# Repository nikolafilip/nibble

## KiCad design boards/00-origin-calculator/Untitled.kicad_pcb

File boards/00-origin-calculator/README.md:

# The origin: a hand-made 3-bit calculator

This is the KiCad project the whole thing started from, exactly as it was on
2026-08-17. Nothing in this directory is edited, ever.

Built by hand, from scratch, while relearning electronics: a keypad encoder, a
3-bit sign-magnitude adder/subtractor built from 2N3904 RTL gates, a result
register, a 4-to-16 decoder for a display, and a reference NOR/NAND pair.
419 transistors, 1,087 resistors. Simulated in KiCad's ngspice integration.

It has bugs. They are listed in `docs/KNOWN-ISSUES.md` and are fixed by the
redesign in `boards/01-alu`, not here.

The SPICE model path inside the schematic points at the Desktop location the
original used; the model is in `lib/2N3904.lib`. The PCB has 747 of about 1,500
footprints placed and no tracks: routing is where the original run stopped.

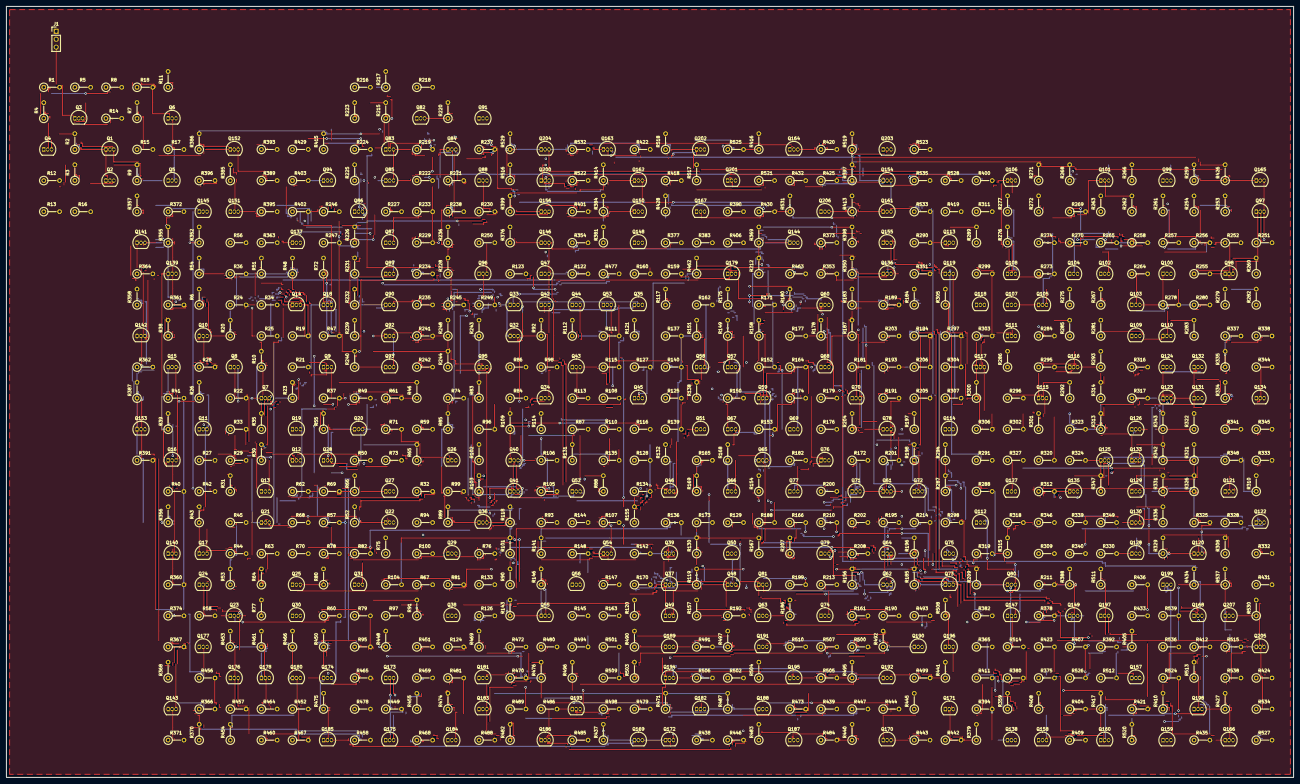
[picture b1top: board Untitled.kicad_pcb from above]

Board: 2 copper layers, 414.0 x 248.0 mm, 747 parts (0 on the bottom side), 386 nets.

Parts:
J1: PWR; PinHeader_1x03_P2.54mm_Vertical
Q1, Q2, Q3, Q4, Q5, Q6, Q7, Q8, Q9, Q10, Q11, Q12, Q13, Q14, Q15, Q16, Q17, Q18, Q19, Q20, Q21, Q22, Q23, Q24, Q25, Q26, Q27, Q28, Q29, Q30, Q31, Q32, Q33, Q34, Q35, Q36, Q37, Q38, Q39, Q40, Q41, Q42, Q43, Q44, Q45, Q46, Q47, Q48, Q49, Q50, Q51, Q52, Q53, Q54, Q55, Q56, Q57, Q58, Q59, Q60, Q61, Q62, Q63, Q64, Q65, Q66, Q67, Q68, Q69, Q70, Q71, Q72, Q73, Q74, Q75, Q76, Q77, Q78, Q79, Q80, Q81, Q82, Q83, Q84, Q85, Q86, Q87, Q88, Q89, Q90, Q91, Q92, Q93, Q94, Q95, Q96, Q97, Q98, Q99, Q100, Q101, Q102, Q103, Q104, Q105, Q106, Q107, Q108, Q109, Q110, Q111, Q112, Q113, Q114, Q115, Q116, Q117, Q118, Q119, Q120, Q121, Q122, Q123, Q124, Q125, Q126, Q127, Q128, Q129, Q130, Q131, Q132, Q133, Q134, Q135, Q136, Q137, Q138, Q139, Q140, Q141, Q142, Q143, Q144, Q145, Q146, Q147, Q148, Q149, Q150, Q151, Q152, Q153, Q154, Q155, Q156, Q157, Q158, Q159, Q160, Q161, Q162, Q163, Q164, Q165, Q166, Q167, Q168, Q169, Q170, Q171, Q172, Q173, Q174, Q175, Q176, Q177, Q178, Q179, Q180, Q181, Q182, Q183, Q184, Q185, Q186, Q187, Q188, Q189, Q190, Q191, Q192, Q193, Q194, Q195, Q196, Q197, Q198, Q199, Q200, Q201, Q202, Q203, Q204, Q205, Q206, Q207: 2N3904; TO-92_Inline
R1, R5, R8, R18, R21, R25, R29, R34, R37, R42, R45, R49, R61, R62, R63, R70, R71, R74, R78, R82, R86, R98, R99, R100, R107, R108, R111, R115, R127, R128, R129, R136, R137, R140, R144, R148, R152, R164, R165, R166, R173, R174, R177, R181, R193, R194, R195, R202, R203, R206, R210, R214, R218, R222, R233, R238, R245, R250, R259, R266, R275, R282, R283, R286, R290, R298, R299, R304, R307, R311, R319, R320, R325, R328, R332, R340, R341, R346, R349, R353, R365, R366, R367, R374, R375, R378, R382, R394, R395, R396, R403, R404, R407, R411, R423, R424, R425, R432, R433, R436, R439, R444, R447, R451, R459, R460, R465, R468, R472, R480, R481, R486, R489, R493, R501, R502, R507, R510, R514, R526, R527, R528, R535, R536, R539: 4.7k; R_Axial_DIN0207_L6.3mm_D2.5mm_P5.08mm_Vertical
R2, R3, R4, R6, R7, R9, R10, R11, R20, R23, R26, R30, R31, R35, R38, R39, R43, R46, R48, R51, R52, R53, R54, R55, R64, R65, R66, R72, R75, R77, R80, R83, R85, R88, R89, R90, R91, R92, R101, R102, R103, R109, R112, R114, R117, R118, R119, R120, R121, R130, R131, R132, R138, R141, R143, R146, R149, R151, R154, R155, R156, R157, R158, R167, R168, R169, R175, R178, R180, R183, R184, R185, R186, R187, R196, R197, R198, R204, R207, R209, R212, R215, R217, R220, R223, R225, R226, R228, R231, R232, R236, R239, R240, R243, R244, R248, R251, R252, R255, R256, R257, R258, R264, R265, R269, R270, R273, R274, R278, R280, R284, R287, R289, R292, R293, R294, R300, R301, R305, R308, R310, R313, R314, R315, R321, R322, R326, R329, R331, R334, R335, R336, R342, R343, R347, R350, R352, R355, R356, R357, R358, R359, R368, R369, R370, R376, R379, R381, R384, R385, R386, R387, R388, R397, R398, R399, R405, R408, R410, R413, R414, R415, R416, R417, R426, R427, R428, R434, R437, R440, R441, R445, R448, R450, R453, R454, R455, R461, R462, R466, R469, R471, R474, R475, R476, R482, R483, R487, R490, R492, R495, R496, R497, R503, R504, R508, R511, R513, R516, R517, R518, R519, R520, R529, R530, R531, R537: 10k; R_Axial_DIN0207_L6.3mm_D2.5mm_P5.08mm_Vertical
R12, R13, R14, R15, R16, R17, R19, R22, R24, R27, R28, R32, R33, R36, R40, R41, R44, R47, R50, R56, R57, R58, R59, R60, R67, R68, R69, R73, R76, R79, R81, R84, R87, R93, R94, R95, R96, R97, R104, R105, R106, R110, R113, R116, R122, R123, R124, R125, R126, R133, R134, R135, R139, R142, R145, R147, R150, R153, R159, R160, R161, R162, R163, R170, R171, R172, R176, R179, R182, R188, R189, R190, R191, R192, R199, R200, R201, R205, R208, R211, R213, R216, R219, R221, R224, R227, R229, R230, R234, R235, R237, R241, R242, R246, R247, R249, R253, R254, R260, R261, R262, R263, R267, R268, R271, R272, R276, R277, R279, R281, R285, R288, R291, R295, R296, R297, R302, R303, R306, R309, R312, R316, R317, R318, R323, R324, R327, R330, R333, R337, R338, R339, R344, R345, R348, R351, R354, R360, R361, R362, R363, R364, R371, R372, R373, R377, R380, R383, R389, R390, R391, R392, R393, R400, R401, R402, R406, R409, R412, R418, R419, R420, R421, R422, R429, R430, R431, R435, R438, R442, R443, R446, R449, R452, R456, R457, R458, R463, R464, R467, R470, R473, R477, R478, R479, R484, R485, R488, R491, R494, R498, R499, R500, R505, R506, R509, R512, R515, R521, R522, R523, R524, R525, R532, R533, R534, R538: 22k; R_Axial_DIN0207_L6.3mm_D2.5mm_P5.08mm_Vertical

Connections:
+5V: J1.2, R1.1, R2.1, R3.1, R5.1, R7.1, R8.1, R9.1, R18.1, R21.1, R25.1, R29.1, R34.1, R37.1, R42.1, R45.1, R49.1, R61.1, R62.1, R63.1, R70.1, R71.1, R74.1, R78.1, R82.1, R86.1, R98.1, R99.1, R100.1, R107.1, R108.1, R111.1, R115.1, R127.1, R128.1, R129.1, R136.1, R137.1, R140.1, R144.1, R148.1, R152.1, R164.1, R165.1, R166.1, R173.1, R174.1, R177.1, R181.1, R193.1, R194.1, R195.1, R202.1, R203.1, R206.1, R210.1, R214.1, R218.1, R222.1, R232.1, R233.1, R238.1, R245.1, R250.1, R255.1, R259.1, R264.1, R266.1, R275.1, R282.1, R283.1, R286.1, R290.1, R298.1, R299.1, R304.1, R307.1, R311.1, R319.1, R320.1, R325.1, R328.1, R332.1, R340.1, R341.1, R346.1, R349.1, R353.1, R365.1, R366.1, R367.1, R374.1, R375.1, R378.1, R382.1, R394.1, R395.1, R396.1, R403.1, R404.1, R407.1, R411.1, R423.1, R424.1, R425.1, R432.1, R433.1, R436.1, R439.1, R444.1, R447.1, R451.1, R459.1, R460.1, R465.1, R468.1, R472.1, R480.1, R481.1, R486.1, R489.1, R493.1, R501.1, R502.1, R507.1, R510.1, R514.1, R526.1, R527.1, R528.1, R535.1, R536.1, R539.1
/A0: Q96.3 (C), R6.1, R10.1, R38.1, R250.2
/A1: Q91.3 (C), R83.1, R88.1, R90.1, R238.2
/A2: Q84.3 (C), R149.1, R154.1, R156.1, R222.2
/B0: Q119.3 (C), R20.1, R26.1, R39.1, R307.2
/B1: Q127.3 (C), R85.1, R89.1, R91.1, R328.2
/B2: Q135.3 (C), R151.1, R155.1, R157.1, R349.2
/Cin1: Q31.3 (C), R82.2, R114.1, R118.1, R120.1
/Cin2: Q56.3 (C), R148.2, R180.1, R184.1, R186.1
/EB0: Q111.3 (C), R286.2, R289.1, R293.1
/EB1: Q110.3 (C), R283.2, R310.1, R314.1
/EB2: Q109.3 (C), R282.2, R331.1, R335.1
/OUT0: Q146.3 (C), R378.2
/OUT1: Q157.3 (C), R407.2
/OUT2: Q168.3 (C), R436.2
/OUT3: Q207.3 (C), R539.2
/OUT4: Q204.3 (C), R535.2
/S0: Q28.3 (C), R74.2, R448.1, R453.1
/S1: Q53.3 (C), R140.2, R469.1, R474.1
/S2: Q78.3 (C), R206.2, R490.1, R495.1
/S3: Q81.3 (C), R214.2, R437.1, R511.1, R516.1, R518.1
/X3: R258.1, R270.1
/X5: R252.1, R273.1
/X7: R251.1, R257.1, R269.1
/Y3: R228.1, R240.1
/Y5: R223.1, R243.1
/Y6: R217.1, R231.1
/Y7: R215.1, R226.1, R239.1
GND: J1.1, Q2.1 (E), Q3.1 (E), Q4.1 (E), Q5.1 (E), Q6.1 (E), Q7.1 (E), Q8.1 (E), Q9.1 (E), Q11.1 (E), Q13.1 (E), Q14.1 (E), Q16.1 (E), Q17.1 (E), Q18.1 (E), Q19.1 (E), Q20.1 (E), Q22.1 (E), Q24.1 (E), Q25.1 (E), Q27.1 (E), Q28.1 (E), Q29.1 (E), Q30.1 (E), Q31.1 (E), Q32.1 (E), Q33.1 (E), Q34.1 (E), Q36.1 (E), Q38.1 (E), Q39.1 (E), Q41.1 (E), Q42.1 (E), Q43.1 (E), Q44.1 (E), Q45.1 (E), Q47.1 (E), Q49.1 (E), Q50.1 (E), Q52.1 (E), Q53.1 (E), Q54.1 (E), Q55.1 (E), Q56.1 (E), Q57.1 (E), Q58.1 (E), Q59.1 (E), Q61.1 (E), Q63.1 (E), Q64.1 (E), Q66.1 (E), Q67.1 (E), Q68.1 (E), Q69.1 (E), Q70.1 (E), Q72.1 (E), Q74.1 (E), Q75.1 (E), Q77.1 (E), Q78.1 (E), Q79.1 (E), Q80.1 (E), Q81.1 (E), Q82.1 (E), Q83.1 (E), Q84.1 (E), Q85.1 (E), Q86.1 (E), Q87.1 (E), Q88.1 (E), Q89.1 (E), Q90.1 (E), Q91.1 (E), Q92.1 (E), Q93.1 (E), Q94.1 (E), Q95.1 (E), Q96.1 (E), Q97.1 (E), Q98.1 (E), Q99.1 (E), Q100.1 (E), Q101.1 (E), Q102.1 (E), Q103.1 (E), Q104.1 (E), Q105.1 (E), Q106.1 (E), Q107.1 (E), Q108.1 (E), Q109.1 (E), Q110.1 (E), Q111.1 (E), Q112.1 (E), Q113.1 (E), Q114.1 (E), Q116.1 (E), Q118.1 (E), Q119.1 (E), Q120.1 (E), Q121.1 (E), Q122.1 (E), Q124.1 (E), Q126.1 (E), Q127.1 (E), Q128.1 (E), Q129.1 (E), Q130.1 (E), Q132.1 (E), Q134.1 (E), Q135.1 (E), Q136.1 (E), Q137.1 (E), Q138.1 (E), Q140.1 (E), Q142.1 (E), Q143.1 (E), Q145.1 (E), Q146.1 (E), Q147.1 (E), Q148.1 (E), Q149.1 (E), Q151.1 (E), Q153.1 (E), Q154.1 (E), Q156.1 (E), Q157.1 (E), Q158.1 (E), Q159.1 (E), Q160.1 (E), Q162.1 (E), Q164.1 (E), Q165.1 (E), Q167.1 (E), Q168.1 (E), Q169.1 (E), Q171.1 (E), Q172.1 (E), Q173.1 (E), Q174.1 (E), Q175.1 (E), Q177.1 (E), Q179.1 (E), Q180.1 (E), Q181.1 (E), Q182.1 (E), Q183.1 (E), Q185.1 (E), Q187.1 (E), Q188.1 (E), Q189.1 (E), Q190.1 (E), Q191.1 (E), Q193.1 (E), Q195.1 (E), Q196.1 (E), Q197.1 (E), Q198.1 (E), Q199.1 (E), Q201.1 (E), Q203.1 (E), Q204.1 (E), Q206.1 (E), Q207.1 (E), R12.1, R13.1, R14.1, R15.1, R16.1, R17.1, R19.1, R22.1, R24.1, R27.1, R28.1, R32.1, R33.1, R36.1, R40.1, R41.1, R44.1, R47.1, R50.1, R56.1, R57.1, R58.1, R59.1, R60.1, R67.1, R68.1, R69.1, R73.1, R76.1, R79.1, R81.1, R84.1, R87.1, R93.1, R94.1, R95.1, R96.1, R97.1, R104.1, R105.1, R106.1, R110.1, R113.1, R116.1, R122.1, R123.1, R124.1, R125.1, R126.1, R133.1, R134.1, R135.1, R139.1, R142.1, R145.1, R147.1, R150.1, R153.1, R159.1, R160.1, R161.1, R162.1, R163.1, R170.1, R171.1, R172.1, R176.1, R179.1, R182.1, R188.1, R189.1, R190.1, R191.1, R192.1, R199.1, R200.1, R201.1, R205.1, R208.1, R211.1, R213.1, R216.1, R219.1, R221.1, R224.1, R227.1, R229.1, R230.1, R234.1, R235.1, R237.1, R241.1, R242.1, R246.1, R247.1, R249.1, R253.1, R254.1, R260.1, R261.1, R262.1, R263.1, R267.1, R268.1, R271.1, R272.1, R276.1, R277.1, R279.1, R281.1, R285.1, R288.1, R291.1, R295.1, R296.1, R297.1, R302.1, R303.1, R306.1, R309.1, R312.1, R316.1, R317.1, R318.1, R323.1, R324.1, R327.1, R330.1, R333.1, R337.1, R338.1, R339.1, R344.1, R345.1, R348.1, R351.1, R354.1, R360.1, R361.1, R362.1, R363.1, R364.1, R371.1, R372.1, R373.1, R377.1, R380.1, R383.1, R389.1, R390.1, R391.1, R392.1, R393.1, R400.1, R401.1, R402.1, R406.1, R409.1, R412.1, R418.1, R419.1, R420.1, R421.1, R422.1, R429.1, R430.1, R431.1, R435.1, R438.1, R442.1, R443.1, R446.1, R449.1, R452.1, R456.1, R457.1, R458.1, R463.1, R464.1, R467.1, R470.1, R473.1, R477.1, R478.1, R479.1, R484.1, R485.1, R488.1, R491.1, R494.1, R498.1, R499.1, R500.1, R505.1, R506.1, R509.1, R512.1, R515.1, R521.1, R522.1, R523.1, R524.1, R525.1, R532.1, R533.1, R534.1, R538.1
unnamed: Q1.2 (B), R2.2, R12.2
unnamed: Q1.3 (C), R1.2, R4.1
unnamed: Q1.1 (E), Q2.3 (C)
unnamed: Q2.2 (B), R3.2, R13.2
unnamed: Q3.2 (B), R4.2, R14.2
unnamed: Q3.3 (C), R5.2
unnamed: Q4.2 (B), R7.2, R15.2
unnamed: Q4.3 (C), Q5.3 (C), R8.2, R11.1
unnamed: Q5.2 (B), R9.2, R16.2
unnamed: Q6.2 (B), R11.2, R17.2
unnamed: Q6.3 (C), R18.2
unnamed: Q7.2 (B), R10.2, R19.2
unnamed: Q7.3 (C), Q8.3 (C), R21.2, R23.1
unnamed: Q8.2 (B), R20.2, R22.2
unnamed: Q9.2 (B), R23.2, R24.2
unnamed: Q9.3 (C), R25.2, R30.1
unnamed: Q10.2 (B), R6.2, R28.2
unnamed: Q10.3 (C), R29.2, R31.1
unnamed: Q10.1 (E), Q11.3 (C)
unnamed: Q11.2 (B), R26.2, R27.2
unnamed: Q12.2 (B), R30.2, R33.2
unnamed: Q12.3 (C), R34.2, R35.1
unnamed: Q12.1 (E), Q13.3 (C)
unnamed: Q13.2 (B), R31.2, R32.2
unnamed: Q14.2 (B), R35.2, R36.2
unnamed: Q14.3 (C), R37.2, R46.1, R51.1, R53.1
unnamed: Q15.2 (B), R38.2, R41.2
unnamed: Q15.3 (C), R42.2, R43.1
unnamed: Q15.1 (E), Q16.3 (C)
unnamed: Q16.2 (B), R39.2, R40.2
unnamed: Q17.2 (B), R43.2, R44.2
unnamed: Q17.3 (C), R45.2, R77.1
unnamed: Q18.2 (B), R46.2, R47.2
unnamed: Q18.3 (C), Q19.3 (C), R49.2, R55.1
unnamed: Q19.2 (B), R48.2, R50.2
unnamed: Q20.2 (B), R55.2, R59.2
unnamed: Q20.3 (C), R61.2, R65.1
unnamed: Q21.2 (B), R51.2, R57.2
unnamed: Q21.3 (C), R62.2, R66.1
unnamed: Q21.1 (E), Q22.3 (C)
unnamed: Q22.2 (B), R52.2, R56.2
unnamed: Q23.2 (B), R53.2, R60.2
unnamed: Q23.3 (C), R63.2, R64.1
unnamed: Q23.1 (E), Q24.3 (C)
unnamed: Q24.2 (B), R54.2, R58.2
unnamed: Q25.2 (B), R64.2, R67.2
unnamed: Q25.3 (C), R70.2, R75.1
unnamed: Q26.2 (B), R65.2, R69.2
unnamed: Q26.3 (C), R71.2, R72.1
unnamed: Q26.1 (E), Q27.3 (C)
unnamed: Q27.2 (B), R66.2, R68.2
unnamed: Q28.2 (B), R72.2, R73.2
unnamed: Q29.2 (B), R75.2, R76.2
unnamed: Q29.3 (C), Q30.3 (C), R78.2, R80.1
unnamed: Q30.2 (B), R77.2, R79.2
unnamed: Q31.2 (B), R80.2, R81.2
unnamed: Q32.2 (B), R83.2, R84.2
unnamed: Q32.3 (C), Q33.3 (C), R86.2, R92.1
unnamed: Q33.2 (B), R85.2, R87.2
unnamed: Q34.2 (B), R92.2, R96.2
unnamed: Q34.3 (C), R98.2, R102.1
unnamed: Q35.2 (B), R88.2, R94.2
unnamed: Q35.3 (C), R99.2, R103.1
unnamed: Q35.1 (E), Q36.3 (C)
unnamed: Q36.2 (B), R89.2, R93.2
unnamed: Q37.2 (B), R90.2, R97.2
unnamed: Q37.3 (C), R100.2, R101.1
unnamed: Q37.1 (E), Q38.3 (C)
unnamed: Q38.2 (B), R91.2, R95.2
unnamed: Q39.2 (B), R101.2, R104.2
unnamed: Q39.3 (C), R107.2, R143.1
unnamed: Q40.2 (B), R102.2, R106.2
unnamed: Q40.3 (C), R108.2, R109.1
unnamed: Q40.1 (E), Q41.3 (C)
unnamed: Q41.2 (B), R103.2, R105.2
unnamed: Q42.2 (B), R109.2, R110.2
unnamed: Q42.3 (C), R111.2, R112.1, R117.1, R119.1
unnamed: Q43.2 (B), R112.2, R113.2
unnamed: Q43.3 (C), Q44.3 (C), R115.2, R121.1
unnamed: Q44.2 (B), R114.2, R116.2
unnamed: Q45.2 (B), R121.2, R125.2
unnamed: Q45.3 (C), R127.2, R131.1
unnamed: Q46.2 (B), R117.2, R123.2
unnamed: Q46.3 (C), R128.2, R132.1
unnamed: Q46.1 (E), Q47.3 (C)
unnamed: Q47.2 (B), R118.2, R122.2
unnamed: Q48.2 (B), R119.2, R126.2
unnamed: Q48.3 (C), R129.2, R130.1
unnamed: Q48.1 (E), Q49.3 (C)
unnamed: Q49.2 (B), R120.2, R124.2
unnamed: Q50.2 (B), R130.2, R133.2
unnamed: Q50.3 (C), R136.2, R141.1
unnamed: Q51.2 (B), R131.2, R135.2
unnamed: Q51.3 (C), R137.2, R138.1
unnamed: Q51.1 (E), Q52.3 (C)
unnamed: Q52.2 (B), R132.2, R134.2
unnamed: Q53.2 (B), R138.2, R139.2
unnamed: Q54.2 (B), R141.2, R142.2
unnamed: Q54.3 (C), Q55.3 (C), R144.2, R146.1
unnamed: Q55.2 (B), R143.2, R145.2
unnamed: Q56.2 (B), R146.2, R147.2
unnamed: Q57.2 (B), R149.2, R150.2
unnamed: Q57.3 (C), Q58.3 (C), R152.2, R158.1
unnamed: Q58.2 (B), R151.2, R153.2
unnamed: Q59.2 (B), R158.2, R162.2
unnamed: Q59.3 (C), R164.2, R168.1
unnamed: Q60.2 (B), R154.2, R160.2
unnamed: Q60.3 (C), R165.2, R169.1
unnamed: Q60.1 (E), Q61.3 (C)
unnamed: Q61.2 (B), R155.2, R159.2
unnamed: Q62.2 (B), R156.2, R163.2
unnamed: Q62.3 (C), R166.2, R167.1
unnamed: Q62.1 (E), Q63.3 (C)
unnamed: Q63.2 (B), R157.2, R161.2
unnamed: Q64.2 (B), R167.2, R170.2
unnamed: Q64.3 (C), R173.2, R209.1
unnamed: Q65.2 (B), R168.2, R172.2
unnamed: Q65.3 (C), R174.2, R175.1
unnamed: Q65.1 (E), Q66.3 (C)
unnamed: Q66.2 (B), R169.2, R171.2
unnamed: Q67.2 (B), R175.2, R176.2
unnamed: Q67.3 (C), R177.2, R178.1, R183.1, R185.1
unnamed: Q68.2 (B), R178.2, R179.2
unnamed: Q68.3 (C), Q69.3 (C), R181.2, R187.1
unnamed: Q69.2 (B), R180.2, R182.2
unnamed: Q70.2 (B), R187.2, R191.2
unnamed: Q70.3 (C), R193.2, R197.1
unnamed: Q71.2 (B), R183.2, R189.2
unnamed: Q71.3 (C), R194.2, R198.1
unnamed: Q71.1 (E), Q72.3 (C)
unnamed: Q72.2 (B), R184.2, R188.2
unnamed: Q73.2 (B), R185.2, R192.2
unnamed: Q73.3 (C), R195.2, R196.1
unnamed: Q73.1 (E), Q74.3 (C)
unnamed: Q74.2 (B), R186.2, R190.2
unnamed: Q75.2 (B), R196.2, R199.2
unnamed: Q75.3 (C), R202.2, R207.1
unnamed: Q76.2 (B), R197.2, R201.2
unnamed: Q76.3 (C), R203.2, R204.1
unnamed: Q76.1 (E), Q77.3 (C)
unnamed: Q77.2 (B), R198.2, R200.2
unnamed: Q78.2 (B), R204.2, R205.2
unnamed: Q79.2 (B), R207.2, R208.2
unnamed: Q79.3 (C), Q80.3 (C), R210.2, R212.1
unnamed: Q80.2 (B), R209.2, R211.2
unnamed: Q81.2 (B), R212.2, R213.2
unnamed: Q82.2 (B), R215.2, R216.2
unnamed: Q82.3 (C), Q83.3 (C), Q85.3 (C), Q86.3 (C), R218.2, R220.1
unnamed: Q83.2 (B), R217.2, R219.2
unnamed: Q84.2 (B), R220.2, R221.2
unnamed: Q85.2 (B), R223.2, R224.2
unnamed: Q86.2 (B), R225.2, R227.2
unnamed: Q87.2 (B), R226.2, R229.2
unnamed: Q87.3 (C), Q88.3 (C), Q89.3 (C), Q90.3 (C), R233.2, R236.1
unnamed: Q88.2 (B), R228.2, R230.2
unnamed: Q89.2 (B), R231.2, R234.2
unnamed: Q90.2 (B), R232.2, R235.2
unnamed: Q91.2 (B), R236.2, R237.2
unnamed: Q92.2 (B), R239.2, R241.2
unnamed: Q92.3 (C), Q93.3 (C), Q94.3 (C), Q95.3 (C), R245.2, R248.1
unnamed: Q93.2 (B), R240.2, R242.2
unnamed: Q94.2 (B), R243.2, R246.2
unnamed: Q95.2 (B), R244.2, R247.2
unnamed: Q96.2 (B), R248.2, R249.2
unnamed: Q97.2 (B), R251.2, R253.2
unnamed: Q98.2 (B), R252.2, R254.2
unnamed: Q99.2 (B), R255.2, R260.2
unnamed: Q100.2 (B), R256.2, R261.2
unnamed: Q97.3 (C), Q98.3 (C), Q99.3 (C), Q100.3 (C), R259.2, R278.1
unnamed: Q101.2 (B), R257.2, R262.2
unnamed: Q101.3 (C), Q102.3 (C), Q103.3 (C), Q104.3 (C), R266.2, R280.1
unnamed: Q102.2 (B), R258.2, R263.2
unnamed: Q103.2 (B), R264.2, R267.2
unnamed: Q104.2 (B), R265.2, R268.2
unnamed: Q105.2 (B), R269.2, R271.2
unnamed: Q105.3 (C), Q106.3 (C), Q107.3 (C), Q108.3 (C), R275.2, R284.1
unnamed: Q106.2 (B), R270.2, R272.2
unnamed: Q107.2 (B), R273.2, R276.2
unnamed: Q108.2 (B), R274.2, R277.2
unnamed: Q109.2 (B), R278.2, R279.2
unnamed: Q110.2 (B), R280.2, R281.2
unnamed: Q111.2 (B), R284.2, R285.2
unnamed: Q112.2 (B), R287.2, R288.2
unnamed: Q112.3 (C), Q113.3 (C), R290.2, R294.1
unnamed: Q113.2 (B), R289.2, R291.2
unnamed: Q114.2 (B), R294.2, R297.2
unnamed: Q114.3 (C), R298.2, R300.1
unnamed: Q115.2 (B), R292.2, R296.2
unnamed: Q115.3 (C), R299.2, R301.1
unnamed: Q115.1 (E), Q116.3 (C)
unnamed: Q116.2 (B), R293.2, R295.2
unnamed: Q117.2 (B), R300.2, R303.2
unnamed: Q117.3 (C), R304.2, R305.1
unnamed: Q117.1 (E), Q118.3 (C)
unnamed: Q118.2 (B), R301.2, R302.2
unnamed: Q119.2 (B), R305.2, R306.2
unnamed: Q120.2 (B), R308.2, R309.2
unnamed: Q120.3 (C), Q121.3 (C), R311.2, R315.1
unnamed: Q121.2 (B), R310.2, R312.2
unnamed: Q122.2 (B), R315.2, R318.2
unnamed: Q122.3 (C), R319.2, R321.1
unnamed: Q123.2 (B), R313.2, R317.2
unnamed: Q123.3 (C), R320.2, R322.1
unnamed: Q123.1 (E), Q124.3 (C)
unnamed: Q124.2 (B), R314.2, R316.2
unnamed: Q125.2 (B), R321.2, R324.2
unnamed: Q125.3 (C), R325.2, R326.1
unnamed: Q125.1 (E), Q126.3 (C)
unnamed: Q126.2 (B), R322.2, R323.2
unnamed: Q127.2 (B), R326.2, R327.2
unnamed: Q128.2 (B), R329.2, R330.2
unnamed: Q128.3 (C), Q129.3 (C), R332.2, R336.1
unnamed: Q129.2 (B), R331.2, R333.2
unnamed: Q130.2 (B), R336.2, R339.2
unnamed: Q130.3 (C), R340.2, R342.1
unnamed: Q131.2 (B), R334.2, R338.2
unnamed: Q131.3 (C), R341.2, R343.1
unnamed: Q131.1 (E), Q132.3 (C)
unnamed: Q132.2 (B), R335.2, R337.2
unnamed: Q133.2 (B), R342.2, R345.2
unnamed: Q133.3 (C), R346.2, R347.1
unnamed: Q133.1 (E), Q134.3 (C)
unnamed: Q134.2 (B), R343.2, R344.2
unnamed: Q135.2 (B), R347.2, R348.2
unnamed: Q136.2 (B), R350.2, R351.2
unnamed: Q136.3 (C), Q137.3 (C), R353.2, R359.1
unnamed: Q137.2 (B), R352.2, R354.2
unnamed: Q138.2 (B), R359.2, R363.2
unnamed: Q138.3 (C), R365.2, R369.1
unnamed: Q139.2 (B), R355.2, R361.2
unnamed: Q139.3 (C), R366.2, R370.1
unnamed: Q139.1 (E), Q140.3 (C)
unnamed: Q140.2 (B), R356.2, R360.2
unnamed: Q141.2 (B), R357.2, R364.2
unnamed: Q141.3 (C), R367.2, R368.1
unnamed: Q141.1 (E), Q142.3 (C)
unnamed: Q142.2 (B), R358.2, R362.2
unnamed: Q143.2 (B), R368.2, R371.2
unnamed: Q143.3 (C), R374.2, R381.1, R385.1, R387.1
unnamed: Q144.2 (B), R369.2, R373.2
unnamed: Q144.3 (C), R375.2, R376.1
unnamed: Q144.1 (E), Q145.3 (C)
unnamed: Q145.2 (B), R370.2, R372.2
unnamed: Q146.2 (B), R376.2, R377.2
unnamed: Q147.2 (B), R379.2, R380.2
unnamed: Q147.3 (C), Q148.3 (C), R382.2, R388.1
unnamed: Q148.2 (B), R381.2, R383.2
unnamed: Q149.2 (B), R388.2, R392.2
unnamed: Q149.3 (C), R394.2, R398.1
unnamed: Q150.2 (B), R384.2, R390.2
unnamed: Q150.3 (C), R395.2, R399.1
unnamed: Q150.1 (E), Q151.3 (C)
unnamed: Q151.2 (B), R385.2, R389.2
unnamed: Q152.2 (B), R386.2, R393.2
unnamed: Q152.3 (C), R396.2, R397.1
unnamed: Q152.1 (E), Q153.3 (C)
unnamed: Q153.2 (B), R387.2, R391.2
unnamed: Q154.2 (B), R397.2, R400.2
unnamed: Q154.3 (C), R403.2, R410.1, R414.1, R416.1
unnamed: Q155.2 (B), R398.2, R402.2
unnamed: Q155.3 (C), R404.2, R405.1
unnamed: Q155.1 (E), Q156.3 (C)
unnamed: Q156.2 (B), R399.2, R401.2
unnamed: Q157.2 (B), R405.2, R406.2
unnamed: Q158.2 (B), R408.2, R409.2
unnamed: Q158.3 (C), Q159.3 (C), R411.2, R417.1
unnamed: Q159.2 (B), R410.2, R412.2
unnamed: Q160.2 (B), R417.2, R421.2
unnamed: Q160.3 (C), R423.2, R427.1
unnamed: Q161.2 (B), R413.2, R419.2
unnamed: Q161.3 (C), R424.2, R428.1
unnamed: Q161.1 (E), Q162.3 (C)
unnamed: Q162.2 (B), R414.2, R418.2
unnamed: Q163.2 (B), R415.2, R422.2
unnamed: Q163.3 (C), R425.2, R426.1
unnamed: Q163.1 (E), Q164.3 (C)
unnamed: Q164.2 (B), R416.2, R420.2
unnamed: Q165.2 (B), R426.2, R429.2
unnamed: Q165.3 (C), R432.2, R513.1, R517.1, R519.1
unnamed: Q166.2 (B), R427.2, R431.2
unnamed: Q166.3 (C), R433.2, R434.1
unnamed: Q166.1 (E), Q167.3 (C)
unnamed: Q167.2 (B), R428.2, R430.2
unnamed: Q168.2 (B), R434.2, R435.2
unnamed: Q169.2 (B), R437.2, R438.2
unnamed: Q169.3 (C), R439.2, R440.1
unnamed: Q170.2 (B), R440.2, R443.2
unnamed: Q170.3 (C), R444.2, R445.1
unnamed: Q170.1 (E), Q171.3 (C)
unnamed: Q171.2 (B), R441.2, R442.2
unnamed: Q172.2 (B), R445.2, R446.2
unnamed: Q173.2 (B), R448.2, R449.2
unnamed: Q173.3 (C), Q174.3 (C), R451.2, R455.1
unnamed: Q174.2 (B), R450.2, R452.2
unnamed: Q175.2 (B), R455.2, R458.2
unnamed: Q175.3 (C), R459.2, R461.1
unnamed: Q176.2 (B), R453.2, R457.2
unnamed: Q176.3 (C), R460.2, R462.1
unnamed: Q176.1 (E), Q177.3 (C)
unnamed: Q177.2 (B), R454.2, R456.2
unnamed: Q178.2 (B), R461.2, R464.2
unnamed: Q178.3 (C), R465.2, R466.1
unnamed: Q178.1 (E), Q179.3 (C)
unnamed: Q179.2 (B), R462.2, R463.2
unnamed: Q180.2 (B), R466.2, R467.2
unnamed: Q180.3 (C), R350.1, R355.1, R357.1, R468.2
unnamed: Q181.2 (B), R469.2, R470.2
unnamed: Q181.3 (C), Q182.3 (C), R472.2, R476.1
unnamed: Q182.2 (B), R471.2, R473.2
unnamed: Q183.2 (B), R476.2, R479.2
unnamed: Q183.3 (C), R480.2, R482.1
unnamed: Q184.2 (B), R474.2, R478.2
unnamed: Q184.3 (C), R481.2, R483.1
unnamed: Q184.1 (E), Q185.3 (C)
unnamed: Q185.2 (B), R475.2, R477.2
unnamed: Q186.2 (B), R482.2, R485.2
unnamed: Q186.3 (C), R486.2, R487.1
unnamed: Q186.1 (E), Q187.3 (C)
unnamed: Q187.2 (B), R483.2, R484.2
unnamed: Q188.2 (B), R487.2, R488.2
unnamed: Q188.3 (C), R379.1, R384.1, R386.1, R489.2
unnamed: Q189.2 (B), R490.2, R491.2
unnamed: Q189.3 (C), Q190.3 (C), R493.2, R497.1
unnamed: Q190.2 (B), R492.2, R494.2
unnamed: Q191.2 (B), R497.2, R500.2
unnamed: Q191.3 (C), R501.2, R503.1
unnamed: Q192.2 (B), R495.2, R499.2
unnamed: Q192.3 (C), R502.2, R504.1
unnamed: Q192.1 (E), Q193.3 (C)
unnamed: Q193.2 (B), R496.2, R498.2
unnamed: Q194.2 (B), R503.2, R506.2
unnamed: Q194.3 (C), R507.2, R508.1
unnamed: Q194.1 (E), Q195.3 (C)
unnamed: Q195.2 (B), R504.2, R505.2
unnamed: Q196.2 (B), R508.2, R509.2
unnamed: Q196.3 (C), R408.1, R413.1, R415.1, R510.2
unnamed: Q197.2 (B), R511.2, R512.2
unnamed: Q197.3 (C), Q198.3 (C), R514.2, R520.1
unnamed: Q198.2 (B), R513.2, R515.2
unnamed: Q199.2 (B), R520.2, R524.2
unnamed: Q199.3 (C), R526.2, R530.1
unnamed: Q200.2 (B), R516.2, R522.2
unnamed: Q200.3 (C), R527.2, R531.1
unnamed: Q200.1 (E), Q201.3 (C)
unnamed: Q201.2 (B), R517.2, R521.2
unnamed: Q202.2 (B), R518.2, R525.2
unnamed: Q202.3 (C), R528.2, R529.1
unnamed: Q202.1 (E), Q203.3 (C)
unnamed: Q203.2 (B), R519.2, R523.2
unnamed: Q204.2 (B), R529.2, R532.2
unnamed: Q205.2 (B), R530.2, R534.2
unnamed: Q205.3 (C), R536.2, R537.1
unnamed: Q205.1 (E), Q206.3 (C)
unnamed: Q206.2 (B), R531.2, R533.2
unnamed: Q207.2 (B), R537.2, R538.2
SIG: Q172.3 (C), R352.1, R356.1, R358.1, R447.2
SUB: J1.3, R48.1, R52.1, R54.1, R287.1, R292.1, R308.1, R313.1, R329.1, R334.1, R441.1, R450.1, R454.1, R471.1, R475.1, R492.1, R496.1

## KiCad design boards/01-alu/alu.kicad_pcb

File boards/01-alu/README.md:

# Board 01: ALU

4-bit ALU: two's-complement adder/subtractor, AND, OR and XOR, with carry and
zero flags. The redesign of the origin calculator's arithmetic (issues #1 to
#4), extended for design v2 (D031) with ONE (B replaced by 0001 for INC and
DEC) and the function lines F1 F0.

| | |
|---|---|
| Transistors | 233 × 2N7000 |
| Resistors | 133 (127 × 47k pull-ups, 6 × 1k for LEDs) |
| LEDs | 6 (R3..R0, CF, ZF) |
| Other | 64-pin bus header, 100 nF + 10 µF decoupling, 4 × M3 holes |
| Bus signals used | in: A0..3, B0..3, SUB, ONE, F0, F1, EO. out: CF, ZF, BUS0#..BUS3# |

With F1 F0 = 00 the result is `R = A + (B xor SUB) + SUB` and `CF` is the carry
out of bit 3 (for a subtraction, 1 means no borrow). F1 F0 = 01, 10, 11 give
A and B, A or B, A xor B, with `CF` = 0. `ONE` replaces B by 0001 first. `ZF`
is 1 when the result is zero. When `EO` is 1 the result is pulled onto the bus
(active-low, open-drain). The logic functions fall out of the adder: the NAND
that makes the generate term is NOT(A and B), the propagate XOR is A xor B, and
A or B is one more NAND of those two.

## Files

- `alu.kicad_sch` — the board, generated by `sim/build_alu.py` from `sim/alu.py`. Do not hand-edit; change `alu.py` and regenerate.
- `alu-testbench.kicad_sch` — stimulus sources, 5 V supply and hub pull-ups so the KiCad simulator runs out of the box. Excluded from the board and BOM.
- `sim_results/` — proof, produced from the kicad-cli export of this exact schematic:
  - `tran_alu_demo.png` — 13 operations, every input and output.
  - `tran_alu_zoom.png` — the carry rippling through all four bits, and 7 − 5.
  - `kicad_exhaustive_{TYP,LO,HI,MIX1}.json` — all 2304 cases at typical, 0.8 V, 3.0 V and mixed threshold corners.
  - `alu_kicad.cir` — the exported netlist that was simulated.

## Verification (2026-09-10, design v2)

| Netlist | Cases | Corner | Result | Worst settle |
|---|---|---|---|---|
| kicad-cli export | 2304 | typical Vth 2.0 V | 2304 / 2304 | 54 µs |
| kicad-cli export | 2304 | Vth 0.8 V | 2304 / 2304 | 28 µs |
| kicad-cli export | 2304 | Vth 3.0 V | 2304 / 2304 | 89 µs |
| kicad-cli export | 2304 | MIX (random threshold per transistor, seed 1) | 2304 / 2304 | 67 µs |

The 2304 cases are every A, B, SUB and function (2048) plus every A with ONE
for both SUB values and all four functions with B = 0 and 15 (256). ERC: 0
violations. Logic levels: high 5.00 V, low under 1 mV on every output.
`sim_results/kicad_exhaustive_*.json` hold the runs; `alu_kicad.cir` is the
netlist that was simulated.

Reproduce from `sim/`:

```
python3 build_alu.py
kicad-cli sch export netlist --format spice -o out/alu_kicad.cir ../boards/01-alu/alu.kicad_sch
python3 tb_alu.py out/alu_kicad.cir out --cases exhaustive --corner HI
python3 tb_alu.py out/alu_kicad.cir out --cases exhaustive --corner MIX --seed 1
python3 tb_alu.py out/alu_kicad.cir out --cases demo && python3 plots_alu.py out/kicad_demo_TYP.dat ../boards/01-alu/sim_results
```

## Not yet done

- PCB re-route for the v2 schematic (the routed `alu.kicad_pcb` in this
  commit is the 137-transistor v1 board).

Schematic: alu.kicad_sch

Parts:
C1: 100n; C_Disc_D5.0mm_W2.5mm_P2.50mm
C2: 10u; CP_Radial_D5.0mm_P2.00mm
D1, D2, D3, D4, D5, D6: LED; LED_D3.0mm
H1, H2, H3, H4: M3; MountingHole_3.2mm_M3_Pad
J1: BUS; IDC-Header_2x32_P2.54mm_Vertical
Q1, Q2, Q3, Q4, Q5, Q6, Q7, Q8, Q9, Q10, Q11, Q12, Q13, Q14, Q15, Q16, Q17, Q18, Q19, Q20, Q21, Q22, Q23, Q24, Q25, Q26, Q27, Q28, Q29, Q30, Q31, Q32, Q33, Q34, Q35, Q36, Q37, Q38, Q39, Q40, Q41, Q42, Q43, Q44, Q45, Q46, Q47, Q48, Q49, Q50, Q51, Q52, Q53, Q54, Q55, Q56, Q57, Q58, Q59, Q60, Q61, Q62, Q63, Q64, Q65, Q66, Q67, Q68, Q69, Q70, Q71, Q72, Q73, Q74, Q75, Q76, Q77, Q78, Q79, Q80, Q81, Q82, Q83, Q84, Q85, Q86, Q87, Q88, Q89, Q90, Q91, Q92, Q93, Q94, Q95, Q96, Q97, Q98, Q99, Q100, Q101, Q102, Q103, Q104, Q105, Q106, Q107, Q108, Q109, Q110, Q111, Q112, Q113, Q114, Q115, Q116, Q117, Q118, Q119, Q120, Q121, Q122, Q123, Q124, Q125, Q126, Q127, Q128, Q129, Q130, Q131, Q132, Q133, Q134, Q135, Q136, Q137, Q138, Q139, Q140, Q141, Q142, Q143, Q144, Q145, Q146, Q147, Q148, Q149, Q150, Q151, Q152, Q153, Q154, Q155, Q156, Q157, Q158, Q159, Q160, Q161, Q162, Q163, Q164, Q165, Q166, Q167, Q168, Q169, Q170, Q171, Q172, Q173, Q174, Q175, Q176, Q177, Q178, Q179, Q180, Q181, Q182, Q183, Q184, Q185, Q186, Q187, Q188, Q189, Q190, Q191, Q192, Q193, Q194, Q195, Q196, Q197, Q198, Q199, Q200, Q201, Q202, Q203, Q204, Q205, Q206, Q207, Q208, Q209, Q210, Q211, Q212, Q213, Q214, Q215, Q216, Q217, Q218, Q219, Q220, Q221, Q222, Q223, Q224, Q225, Q226, Q227, Q228, Q229, Q230, Q231, Q232, Q233: 2N7000; TO-92_Inline_Wide
R1, R2, R3, R4, R5, R6, R7, R8, R9, R10, R11, R12, R13, R14, R15, R16, R17, R18, R19, R20, R21, R22, R23, R24, R25, R26, R27, R28, R29, R30, R31, R32, R33, R34, R35, R36, R37, R38, R39, R40, R41, R42, R43, R44, R45, R46, R47, R48, R49, R50, R51, R52, R53, R54, R55, R56, R57, R58, R59, R60, R61, R62, R63, R64, R65, R66, R67, R68, R69, R70, R71, R72, R73, R74, R75, R76, R77, R78, R79, R80, R81, R82, R83, R84, R85, R86, R87, R88, R89, R90, R91, R92, R93, R94, R95, R96, R97, R98, R99, R100, R101, R102, R103, R104, R105, R106, R107, R108, R109, R110, R111, R112, R113, R114, R115, R116, R117, R118, R119, R120, R121, R122, R123, R124, R125, R126, R127: 47k; R_Axial_DIN0207_L6.3mm_D2.5mm_P5.08mm_Vertical
R128, R129, R130, R131, R132, R133: 1k; R_Axial_DIN0207_L6.3mm_D2.5mm_P5.08mm_Vertical

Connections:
+5V: C1.1, C2.1, J1.1, J1.2, J1.63, R1.1, R2.1, R3.1, R4.1, R5.1, R6.1, R7.1, R8.1, R9.1, R10.1, R11.1, R12.1, R13.1, R14.1, R15.1, R16.1, R17.1, R18.1, R19.1, R20.1, R21.1, R22.1, R23.1, R24.1, R25.1, R26.1, R27.1, R28.1, R29.1, R30.1, R31.1, R32.1, R33.1, R34.1, R35.1, R36.1, R37.1, R38.1, R39.1, R40.1, R41.1, R42.1, R43.1, R44.1, R45.1, R46.1, R47.1, R48.1, R49.1, R50.1, R51.1, R52.1, R53.1, R54.1, R55.1, R56.1, R57.1, R58.1, R59.1, R60.1, R61.1, R62.1, R63.1, R64.1, R65.1, R66.1, R67.1, R68.1, R69.1, R70.1, R71.1, R72.1, R73.1, R74.1, R75.1, R76.1, R77.1, R78.1, R79.1, R80.1, R81.1, R82.1, R83.1, R84.1, R85.1, R86.1, R87.1, R88.1, R89.1, R90.1, R91.1, R92.1, R93.1, R94.1, R95.1, R96.1, R97.1, R98.1, R99.1, R100.1, R101.1, R102.1, R103.1, R104.1, R105.1, R106.1, R107.1, R108.1, R109.1, R110.1, R111.1, R112.1, R113.1, R114.1, R115.1, R116.1, R117.1, R118.1, R119.1, R120.1, R121.1, R122.1, R123.1, R124.1, R125.1, R126.1, R127.1, R128.1, R129.1, R130.1, R131.1, R132.1, R133.1
A0: J1.13, Q42.2 (G), Q44.2 (G), Q56.2 (G)
A1: J1.14, Q62.2 (G), Q64.2 (G), Q76.2 (G)
A2: J1.15, Q82.2 (G), Q84.2 (G), Q96.2 (G)
A3: J1.16, Q102.2 (G), Q104.2 (G), Q116.2 (G)
AND0: Q133.3 (D), Q140.2 (G), R77.2
AND1: Q151.3 (D), Q158.2 (G), R87.2
AND2: Q169.3 (D), Q176.2 (G), R97.2
AND3: Q187.3 (D), Q194.2 (G), R107.2
B0: J1.17, Q2.2 (G), Q3.2 (G)
B1: J1.18, Q12.2 (G)
B2: J1.19, Q22.2 (G)
B3: J1.20, Q32.2 (G)
BB0: Q5.3 (D), Q6.2 (G), R4.2
BB0N: Q3.3 (D), Q4.3 (D), Q5.2 (G), Q8.2 (G), R3.2
BB1: Q13.3 (D), Q14.3 (D), Q15.2 (G), Q16.2 (G), R9.2
BB1N: Q15.3 (D), Q18.2 (G), R10.2
BB2: Q23.3 (D), Q24.3 (D), Q25.2 (G), Q26.2 (G), R15.2
BB2N: Q25.3 (D), Q28.2 (G), R16.2
BB3: Q33.3 (D), Q34.3 (D), Q35.2 (G), Q36.2 (G), R21.2
BB3N: Q35.3 (D), Q38.2 (G), R22.2
BD0: Q214.3 (D), Q215.2 (G), R121.2
BD1: Q218.3 (D), Q219.2 (G), R123.2
BD2: Q222.3 (D), Q223.2 (G), R125.2
BD3: Q226.3 (D), Q227.2 (G), R127.2
BDN0: Q212.3 (D), Q214.2 (G), R120.2
BDN1: Q216.3 (D), Q218.2 (G), R122.2
BDN2: Q220.3 (D), Q222.2 (G), R124.2
BDN3: Q224.3 (D), Q226.2 (G), R126.2
BN0: Q2.3 (D), R2.2
BN1: Q12.3 (D), Q13.2 (G), R8.2
BN2: Q22.3 (D), Q23.2 (G), R14.2
BN3: Q32.3 (D), Q33.2 (G), R20.2
BUS0#: J1.9, Q215.3 (D)
BUS1#: J1.10, Q219.3 (D)
BUS2#: J1.11, Q223.3 (D)
BUS3#: J1.12, Q227.3 (D)
C1: Q60.3 (D), Q70.2 (G), Q72.2 (G), Q79.2 (G), R36.2
C2: Q80.3 (D), Q90.2 (G), Q92.2 (G), Q99.2 (G), R47.2
C3: Q100.3 (D), Q110.2 (G), Q112.2 (G), Q119.2 (G), R58.2
C4: Q120.3 (D), Q205.2 (G), R69.2
CF: J1.37, Q207.3 (D), Q232.2 (G), R118.2
CFN: Q205.3 (D), Q207.2 (G), R117.2
EO: J1.40, Q213.2 (G), Q217.2 (G), Q221.2 (G), Q225.2 (G)
F0: J1.60, Q122.2 (G), Q125.2 (G), Q129.2 (G), Q131.2 (G)
F0N: Q122.3 (D), Q127.2 (G), R70.2
F1: J1.61, Q123.2 (G), Q124.2 (G), Q126.2 (G), Q130.2 (G)
F1N: Q123.3 (D), Q128.2 (G), R71.2
FA: Q126.3 (D), Q127.3 (D), Q139.2 (G), Q157.2 (G), Q175.2 (G), Q193.2 (G), R73.2
FO: Q128.3 (D), Q129.3 (D), Q141.2 (G), Q159.2 (G), Q177.2 (G), Q195.2 (G), R74.2
FS: Q124.3 (D), Q125.3 (D), Q137.2 (G), Q155.2 (G), Q173.2 (G), Q191.2 (G), Q206.2 (G), R72.2
FX: Q132.3 (D), Q143.2 (G), Q161.2 (G), Q179.2 (G), Q197.2 (G), R76.2
FXN: Q130.3 (D), Q132.2 (G), R75.2
G0: Q56.3 (D), Q60.2 (G), Q133.2 (G), Q136.2 (G), R34.2
G1: Q76.3 (D), Q80.2 (G), Q151.2 (G), Q154.2 (G), R45.2
G2: Q96.3 (D), Q100.2 (G), Q169.2 (G), Q172.2 (G), R56.2
G3: Q116.3 (D), Q120.2 (G), Q187.2 (G), Q190.2 (G), R67.2
GND: C1.2, C2.2, J1.3, J1.4, J1.6, J1.8, J1.64, Q1.1 (S), Q2.1 (S), Q3.1 (S), Q4.1 (S), Q5.1 (S), Q7.1 (S), Q9.1 (S), Q11.1 (S), Q12.1 (S), Q13.1 (S), Q14.1 (S), Q15.1 (S), Q17.1 (S), Q19.1 (S), Q21.1 (S), Q22.1 (S), Q23.1 (S), Q24.1 (S), Q25.1 (S), Q27.1 (S), Q29.1 (S), Q31.1 (S), Q32.1 (S), Q33.1 (S), Q34.1 (S), Q35.1 (S), Q37.1 (S), Q39.1 (S), Q41.1 (S), Q42.1 (S), Q43.1 (S), Q45.1 (S), Q46.1 (S), Q47.1 (S), Q48.1 (S), Q49.1 (S), Q50.1 (S), Q52.1 (S), Q53.1 (S), Q54.1 (S), Q55.1 (S), Q57.1 (S), Q59.1 (S), Q61.1 (S), Q62.1 (S), Q63.1 (S), Q65.1 (S), Q66.1 (S), Q67.1 (S), Q68.1 (S), Q69.1 (S), Q70.1 (S), Q72.1 (S), Q73.1 (S), Q74.1 (S), Q75.1 (S), Q77.1 (S), Q79.1 (S), Q81.1 (S), Q82.1 (S), Q83.1 (S), Q85.1 (S), Q86.1 (S), Q87.1 (S), Q88.1 (S), Q89.1 (S), Q90.1 (S), Q92.1 (S), Q93.1 (S), Q94.1 (S), Q95.1 (S), Q97.1 (S), Q99.1 (S), Q101.1 (S), Q102.1 (S), Q103.1 (S), Q105.1 (S), Q106.1 (S), Q107.1 (S), Q108.1 (S), Q109.1 (S), Q110.1 (S), Q112.1 (S), Q113.1 (S), Q114.1 (S), Q115.1 (S), Q117.1 (S), Q119.1 (S), Q121.1 (S), Q122.1 (S), Q123.1 (S), Q124.1 (S), Q125.1 (S), Q126.1 (S), Q127.1 (S), Q128.1 (S), Q129.1 (S), Q131.1 (S), Q132.1 (S), Q133.1 (S), Q134.1 (S), Q136.1 (S), Q138.1 (S), Q140.1 (S), Q142.1 (S), Q144.1 (S), Q147.1 (S), Q148.1 (S), Q150.1 (S), Q151.1 (S), Q152.1 (S), Q154.1 (S), Q156.1 (S), Q158.1 (S), Q160.1 (S), Q162.1 (S), Q165.1 (S), Q166.1 (S), Q168.1 (S), Q169.1 (S), Q170.1 (S), Q172.1 (S), Q174.1 (S), Q176.1 (S), Q178.1 (S), Q180.1 (S), Q183.1 (S), Q184.1 (S), Q186.1 (S), Q187.1 (S), Q188.1 (S), Q190.1 (S), Q192.1 (S), Q194.1 (S), Q196.1 (S), Q198.1 (S), Q201.1 (S), Q202.1 (S), Q204.1 (S), Q206.1 (S), Q207.1 (S), Q208.1 (S), Q209.1 (S), Q210.1 (S), Q211.1 (S), Q213.1 (S), Q214.1 (S), Q215.1 (S), Q217.1 (S), Q218.1 (S), Q219.1 (S), Q221.1 (S), Q222.1 (S), Q223.1 (S), Q225.1 (S), Q226.1 (S), Q227.1 (S), Q228.1 (S), Q229.1 (S), Q230.1 (S), Q231.1 (S), Q232.1 (S), Q233.1 (S)
unnamed: D1.2 (A), R128.2
unnamed: D1.1 (K), Q228.3 (D)
unnamed: D2.2 (A), R129.2
unnamed: D2.1 (K), Q229.3 (D)
unnamed: D3.2 (A), R130.2
unnamed: D3.1 (K), Q230.3 (D)
unnamed: D4.2 (A), R131.2
unnamed: D4.1 (K), Q231.3 (D)
unnamed: D5.2 (A), R132.2
unnamed: D5.1 (K), Q232.3 (D)
unnamed: D6.2 (A), R133.2
unnamed: D6.1 (K), Q233.3 (D)
unnamed: Q6.1 (S), Q7.3 (D)
unnamed: Q8.1 (S), Q9.3 (D)
unnamed: Q10.1 (S), Q11.3 (D)
unnamed: Q16.1 (S), Q17.3 (D)
unnamed: Q18.1 (S), Q19.3 (D)
unnamed: Q20.1 (S), Q21.3 (D)
unnamed: Q26.1 (S), Q27.3 (D)
unnamed: Q28.1 (S), Q29.3 (D)
unnamed: Q30.1 (S), Q31.3 (D)
unnamed: Q36.1 (S), Q37.3 (D)
unnamed: Q38.1 (S), Q39.3 (D)
unnamed: Q40.1 (S), Q41.3 (D)
unnamed: Q44.1 (S), Q45.3 (D)
unnamed: Q51.1 (S), Q52.3 (D)
unnamed: Q56.1 (S), Q57.3 (D)
unnamed: Q58.1 (S), Q59.3 (D)
unnamed: Q60.1 (S), Q61.3 (D)
unnamed: Q64.1 (S), Q65.3 (D)
unnamed: Q71.1 (S), Q72.3 (D)
unnamed: Q76.1 (S), Q77.3 (D)
unnamed: Q78.1 (S), Q79.3 (D)
unnamed: Q80.1 (S), Q81.3 (D)
unnamed: Q84.1 (S), Q85.3 (D)
unnamed: Q91.1 (S), Q92.3 (D)
unnamed: Q96.1 (S), Q97.3 (D)
unnamed: Q98.1 (S), Q99.3 (D)
unnamed: Q100.1 (S), Q101.3 (D)
unnamed: Q104.1 (S), Q105.3 (D)
unnamed: Q111.1 (S), Q112.3 (D)
unnamed: Q116.1 (S), Q117.3 (D)
unnamed: Q118.1 (S), Q119.3 (D)
unnamed: Q120.1 (S), Q121.3 (D)
unnamed: Q130.1 (S), Q131.3 (D)
unnamed: Q135.1 (S), Q136.3 (D)
unnamed: Q137.1 (S), Q138.3 (D)
unnamed: Q139.1 (S), Q140.3 (D)
unnamed: Q141.1 (S), Q142.3 (D)
unnamed: Q143.1 (S), Q144.3 (D)
unnamed: Q145.1 (S), Q146.3 (D)
unnamed: Q146.1 (S), Q147.3 (D)
unnamed: Q149.1 (S), Q150.3 (D)
unnamed: Q153.1 (S), Q154.3 (D)
unnamed: Q155.1 (S), Q156.3 (D)
unnamed: Q157.1 (S), Q158.3 (D)
unnamed: Q159.1 (S), Q160.3 (D)
unnamed: Q161.1 (S), Q162.3 (D)
unnamed: Q163.1 (S), Q164.3 (D)
unnamed: Q164.1 (S), Q165.3 (D)
unnamed: Q167.1 (S), Q168.3 (D)
unnamed: Q171.1 (S), Q172.3 (D)
unnamed: Q173.1 (S), Q174.3 (D)
unnamed: Q175.1 (S), Q176.3 (D)
unnamed: Q177.1 (S), Q178.3 (D)
unnamed: Q179.1 (S), Q180.3 (D)
unnamed: Q181.1 (S), Q182.3 (D)
unnamed: Q182.1 (S), Q183.3 (D)
unnamed: Q185.1 (S), Q186.3 (D)
unnamed: Q189.1 (S), Q190.3 (D)
unnamed: Q191.1 (S), Q192.3 (D)
unnamed: Q193.1 (S), Q194.3 (D)
unnamed: Q195.1 (S), Q196.3 (D)
unnamed: Q197.1 (S), Q198.3 (D)
unnamed: Q199.1 (S), Q200.3 (D)
unnamed: Q200.1 (S), Q201.3 (D)
unnamed: Q203.1 (S), Q204.3 (D)
unnamed: Q205.1 (S), Q206.3 (D)
unnamed: Q212.1 (S), Q213.3 (D)
unnamed: Q216.1 (S), Q217.3 (D)
unnamed: Q220.1 (S), Q221.3 (D)
unnamed: Q224.1 (S), Q225.3 (D)
ONE: J1.59, Q4.2 (G), Q14.2 (G), Q24.2 (G), Q34.2 (G)
OR0: Q135.3 (D), Q142.2 (G), R79.2
OR1: Q153.3 (D), Q160.2 (G), R89.2
OR2: Q171.3 (D), Q178.2 (G), R99.2
OR3: Q189.3 (D), Q196.2 (G), R109.2
P0: Q47.3 (D), Q48.3 (D), Q49.2 (G), Q51.2 (G), Q58.2 (G), Q134.2 (G), Q144.2 (G), R29.2
P0_a: Q44.3 (D), Q46.2 (G), R27.2
P0_d: Q46.3 (D), Q48.2 (G), R28.2
P0_n: Q42.3 (D), Q43.3 (D), Q47.2 (G), R26.2
P1: Q67.3 (D), Q68.3 (D), Q69.2 (G), Q71.2 (G), Q78.2 (G), Q152.2 (G), Q162.2 (G), R40.2
P1_a: Q64.3 (D), Q66.2 (G), R38.2
P1_d: Q66.3 (D), Q68.2 (G), R39.2
P1_n: Q62.3 (D), Q63.3 (D), Q67.2 (G), R37.2
P2: Q87.3 (D), Q88.3 (D), Q89.2 (G), Q91.2 (G), Q98.2 (G), Q170.2 (G), Q180.2 (G), R51.2
P2_a: Q84.3 (D), Q86.2 (G), R49.2
P2_d: Q86.3 (D), Q88.2 (G), R50.2
P2_n: Q82.3 (D), Q83.3 (D), Q87.2 (G), R48.2
P3: Q107.3 (D), Q108.3 (D), Q109.2 (G), Q111.2 (G), Q118.2 (G), Q188.2 (G), Q198.2 (G), R62.2
P3_a: Q104.3 (D), Q106.2 (G), R60.2
P3_d: Q106.3 (D), Q108.2 (G), R61.2
P3_n: Q102.3 (D), Q103.3 (D), Q107.2 (G), R59.2
PN0: Q134.3 (D), Q135.2 (G), R78.2
PN1: Q152.3 (D), Q153.2 (G), R88.2
PN2: Q170.3 (D), Q171.2 (G), R98.2
PN3: Q188.3 (D), Q189.2 (G), R108.2
R0: Q149.3 (D), Q208.2 (G), Q212.2 (G), Q231.2 (G), R86.2
R1: Q167.3 (D), Q209.2 (G), Q216.2 (G), Q230.2 (G), R96.2
R2: Q185.3 (D), Q210.2 (G), Q220.2 (G), Q229.2 (G), R106.2
R3: Q203.3 (D), Q211.2 (G), Q224.2 (G), Q228.2 (G), R116.2
RA0: Q139.3 (D), Q146.2 (G), R81.2
RA1: Q157.3 (D), Q164.2 (G), R91.2
RA2: Q175.3 (D), Q182.2 (G), R101.2
RA3: Q193.3 (D), Q200.2 (G), R111.2
RM0: Q145.3 (D), Q148.2 (G), R84.2
RM1: Q163.3 (D), Q166.2 (G), R94.2
RM2: Q181.3 (D), Q184.2 (G), R104.2
RM3: Q199.3 (D), Q202.2 (G), R114.2
RMN0: Q148.3 (D), Q149.2 (G), R85.2
RMN1: Q166.3 (D), Q167.2 (G), R95.2
RMN2: Q184.3 (D), Q185.2 (G), R105.2
RMN3: Q202.3 (D), Q203.2 (G), R115.2
RO0: Q141.3 (D), Q147.2 (G), R82.2
RO1: Q159.3 (D), Q165.2 (G), R92.2
RO2: Q177.3 (D), Q183.2 (G), R102.2
RO3: Q195.3 (D), Q201.2 (G), R112.2
RS0: Q137.3 (D), Q145.2 (G), R80.2
RS1: Q155.3 (D), Q163.2 (G), R90.2
RS2: Q173.3 (D), Q181.2 (G), R100.2
RS3: Q191.3 (D), Q199.2 (G), R110.2
RX0: Q143.3 (D), Q150.2 (G), R83.2
RX1: Q161.3 (D), Q168.2 (G), R93.2
RX2: Q179.3 (D), Q186.2 (G), R103.2
RX3: Q197.3 (D), Q204.2 (G), R113.2
S0: Q54.3 (D), Q55.3 (D), Q138.2 (G), R33.2
S0_a: Q51.3 (D), Q53.2 (G), R31.2
S0_d: Q53.3 (D), Q55.2 (G), R32.2
S0_n: Q49.3 (D), Q50.3 (D), Q54.2 (G), R30.2
S1: Q74.3 (D), Q75.3 (D), Q156.2 (G), R44.2
S1_a: Q71.3 (D), Q73.2 (G), R42.2
S1_d: Q73.3 (D), Q75.2 (G), R43.2
S1_n: Q69.3 (D), Q70.3 (D), Q74.2 (G), R41.2
S2: Q94.3 (D), Q95.3 (D), Q174.2 (G), R55.2
S2_a: Q91.3 (D), Q93.2 (G), R53.2
S2_d: Q93.3 (D), Q95.2 (G), R54.2
S2_n: Q89.3 (D), Q90.3 (D), Q94.2 (G), R52.2
S3: Q114.3 (D), Q115.3 (D), Q192.2 (G), R66.2
S3_a: Q111.3 (D), Q113.2 (G), R64.2
S3_d: Q113.3 (D), Q115.2 (G), R65.2
S3_n: Q109.3 (D), Q110.3 (D), Q114.2 (G), R63.2
SUB: J1.39, Q1.2 (G), Q9.2 (G), Q19.2 (G), Q29.2 (G), Q39.2 (G), Q50.2 (G), Q52.2 (G), Q59.2 (G)
SUBN: Q1.3 (D), Q7.2 (G), Q17.2 (G), Q27.2 (G), Q37.2 (G), R1.2
T0: Q58.3 (D), Q61.2 (G), R35.2
T1: Q78.3 (D), Q81.2 (G), R46.2
T2: Q98.3 (D), Q101.2 (G), R57.2
T3: Q118.3 (D), Q121.2 (G), R68.2
XB0: Q10.3 (D), Q43.2 (G), Q45.2 (G), Q57.2 (G), R7.2
XB1: Q20.3 (D), Q63.2 (G), Q65.2 (G), Q77.2 (G), R13.2
XB2: Q30.3 (D), Q83.2 (G), Q85.2 (G), Q97.2 (G), R19.2
XB3: Q40.3 (D), Q103.2 (G), Q105.2 (G), Q117.2 (G), R25.2
XBA0: Q6.3 (D), Q10.2 (G), R5.2
XBA1: Q16.3 (D), Q20.2 (G), R11.2
XBA2: Q26.3 (D), Q30.2 (G), R17.2
XBA3: Q36.3 (D), Q40.2 (G), R23.2
XBB0: Q8.3 (D), Q11.2 (G), R6.2
XBB1: Q18.3 (D), Q21.2 (G), R12.2
XBB2: Q28.3 (D), Q31.2 (G), R18.2
XBB3: Q38.3 (D), Q41.2 (G), R24.2
ZF: J1.38, Q208.3 (D), Q209.3 (D), Q210.3 (D), Q211.3 (D), Q233.2 (G), R119.2

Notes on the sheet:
NIBBLE BOARD 01 - ALU: 4-bit adder/subtractor, AND, OR, XOR, with carry and zero flags
Cell: 2N7000 + 47k pull-up (NMOS, see docs/gate-cell.md). 233 transistors, 133 resistors, 6 LEDs. Inputs from the bus header: A3..A0, B3..B0 (register contents), SUB (1 = subtract), ONE (B input replaced by 0001: INC, DEC), F1 F0 (function), EO (1 = drive the result onto the bus). Outputs: CF (carr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
Decoupling
Mounting holes
B INPUT: BB = B, or 0001 when ONE=1 (INC, DEC). Then the conditional invert: XB = BB when SUB=0, NOT BB when SUB=1 (two's complement: A - B = A + NOT B + 1, the +1 is SUB fed into the carry-in)
RIPPLE-CARRY FULL ADDERS, bit 0 to bit 3: P = A xor XB, S = P xor Cin, Cout = A.XB + P.Cin. G = NAND(A, XB) is also NOT (A and XB), P is A xor XB, and A or XB = NAND(NOT P, G): the logic functions fall out of the adder
FUNCTION DECODE: FS = add/sub (F1 F0 = 00), FA = and (01), FO = or (10), FX = xor (11)
RESULT SELECT, per bit: R = FS.S + FA.AND + FO.OR + FX.P. NAND-NAND form with the four-way OR split as NAND3 then NAND2 (never more than three transistors in series)
FLAGS: CF = carry out of bit 3, only for add/sub (0 for the logic functions); ZF = all result bits zero
BUS DRIVERS: pull BUS_i# low when EO=1 and R_i=1 (open drain, pull-ups live on the hub board)
INDICATORS: result R3..R0, CF, ZF
LED_R3
LED_R2
LED_R1
LED_R0
LED_CF
LED_ZF
